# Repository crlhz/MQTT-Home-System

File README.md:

# MQTT Home System

**MQTT Home** is an MQTT based IoT system, developed for the master's thesis. It is a set of devices and programs, which allows to measure physical quantities and control typical home devices. The application of an open-source protocol, such as MQTT, allows a user to add any compatible device to the existing IoT network and gives much more control over transmission and security. The core of the MQTT Home System is **Raspberry Pi**, which runs MQTT Broker, the database and website for measurement presentations and client device’s control. Wireless communication between broker and clients is ensured by a router. A diagram of the example network with three client devices is presented below.

# Client Device - Colibri

The client device, called Colibri, is a microprocessor appliance designed from scratch, providing the measuring and executive functions. For purposes of this thesis, three clients have been assembled and communicated with Raspberry Pi via MQTT protocol. 

## Colibri HW
Colibri is a battery-powered device, which consists of two parts: Power Management Block and CPU Block.

The following inputs/outputs are available for user: 
- J1 - connector for battery charger;
- J2 - UART interface, used for programming device;
- J3 - 1-wire interface, here used as a interface for external temperature sensor;
- J4 - used for enabling deep sleep mode: 1 - 2: sleep mode, 2 - 3: no sleep mode;
- J5 - used for setting boot mode: 1 - 2: standard mode, 2 - 3: programming mode;
- J6 - connector for controlling additional devices (not used in this implementation);
- J7 - connector for 18650 Li-ion battery.

The Power Management Block is responsible for battery charging control and voltage adjustment for the CPU Block. Controller U3 is protecting the battery from being overcharged or over-discharged, by switching U4 and U5 MOSFET transistors, while voltage regulator U6 ensures 3.3V for the CPU Block. The CPU block is responsible for external devices maintenance and broker communication. It’s based on ESP8266 microcontroller, version ESP12 F, which provides a PCB antenna for WiFi transmission. The external resistors are necessary for proper microcontroller operation and they are connected according to the ESP datasheet. A voltage divider, which consists of resistors R8 and R9, is used for measuring battery voltage level. The Colibri software algorithm is presented below.

## Colibri SW
The configuration part allows a user to change topic names and network details, such as SSID, password, broker IP address, and client’s name. After typical variables and interfaces initialization, the program enters an infinite loop, where connection with a broker is established and the measured temperature and voltage is sent to the broker. Finally, the device is going into deep sleep mode for 20 minutes. The described algorithm ensures an acceptable battery life cycle, which can be extended by increasing the sleep time.

## Colibri PCB
Colibri’s PCB has been designed using Kicad software. It is a two layers PCB, which has been assembled by the reflow soldering method. The PCB is enclosed in a KRADEX ABS housing, which provides IP65 protection.

# Broker and subscriber script

The main component of the system is Raspberry Pi, running an MQTT broker called Mosquito, created by the Eclipse Foundation. It’s an open-source implementation of a server for versions 5.0, 3.1.1, and 3.1 of the MQTT protocol. Independently of it, a Python script, called *mqtt_sub_basic.py*, is running on the server. To be more precise, it is a client script, which subscribes to all topics, using the Eclipse Paho MQTT library, also created by Eclipse Foundation. In the beginning, the subscriber script establishes communication with the Mosquito broker and SQL database. Then, by using *client.subscribe("#")*, the script begins subscription of all topics, served by broker. Finally, in an infinite loop, *mqtt_subscribe.py* waits for messages sent by clients in format shown below:

    <topic name>, <measured value>
e.g
    
    blue/temp/out, 22.7
 
Messages received from clients are parsed and then inserted into the SQL database, using methods from the Database class (*db_controller.py* file). This mentioned class is based on the *mysql.connector* library, which allows sending SQL statements from Python scripts to a database. The *mqtt_sub_basic.py* script should be configured as a service, running in the Raspberry Pi’s background, so it starts at every boot-up of the operating system.

# MQTT Home database

The MQTT Home database consists of five tables. It has been developed using a migration mechanism, shared by PHP web framework Laravel. The three tables *users*, *migrations*, *personal_access_tokens* are default Laravel composition, which allows user and migration management. Furthermore, the table users has been implemented, with future development needs in mind, such as adding new topics via the website by logged-in users. The table *topics* stores available topic names, which can be used by client devices. For this system, the following topic format has been adopted.

Additionally, for convenient data presentation, the column unit has been defined in the topics table. The table measurements stores data received from clients via the mentioned Python script.

# MQTT Home website

The MQTT Home website is another important component of the entire system. Its main goal is to present collected data in a user-friendly and convenient way. Furthermore, in case of future development, it may provide some setup functionality, such as topics and users configuration. The website has been created using Laravel, an open-source PHP framework, designed according to the model-view-controller (MVC) architectural pattern. This improves its scalability and resolves many development issues related to cybersecurity, database connections, etc. The homepage, follows a grid layout, which is dynamically generated depending on the topic’s number. Each box stands for a single topic and contains the latest measurement. In a case of communication loss (i.e., 20 minutes or more without a new message), the label N/A is displayed. Apart from values, the boxes include topic names and units.

By clicking on a specific box, the user is able to open the chart view. The charts implementation is based on the Highcharts library. For the sake of clarity of the chart, the displayed data are from the last three days only.

The website’s project consists of three controllers: *Controller.php*, which is created by default as a Laravel Base Controller, together with *MainController.php* and *ChartController.php*, that form the core of the whole application. Both are responsible for retrieving data from the database, processing them into appropriate form and passing to the frontend section. This section is developed by using the Blade templates engine. In the *app.blade.php* file, the overall template of the website was designed, while in *main.blade.php* and *chart.blade.php* the specific content of both views is described. As mentioned before, the homepage consists of boxes representing every available topic. Clicking on any of them redirects to *home.test/chart/n*, where *n* stands for the topic identifier. At this address, a chart related to the chosen topic is displayed. The website project scheme is presented below.

# Server configuration
The last but not least element of the MQTT Home System is the server system. It provides the following functionality: 
- running MQTT broker service;
- receiving data from clients;
- storing received data in the SQL database;
- running WWW service;
- presenting stored data on the website. 

Considering the price and energy consumption, the Raspberry Pi 4B SBC was chosen as the server hardware. This particular SBC is equipped with 4GB of RAM and runs a 1.5 GHz, 64-bit quad core ARM Cortex-A72 processor. Its capabilities exceed the current requirements of this application, but it may be an optimal choice for future development. As mentioned before, the MQTT broker service is run by Eclipse Mosquitto, installed according to the instructions described in the documentation. Afterwards, the default configuration has been applied. In the next step, Python v3.9.2 with *paho.mqtt.client* and *mysql.connector* libraries have been installed. MariaDB v10.5.12 was used as a relational database management system in connection with the phpMyAdmin service. The WWW server functionality has been built upon the LAMP software stack: Linux + Apache + MariaDB + PHP. Therefore, the last step was to install Apache v2.4.52 and PHP v8.1.3. The MQTT Home System website is running as an Apache virtual host on the default TCP port 80.

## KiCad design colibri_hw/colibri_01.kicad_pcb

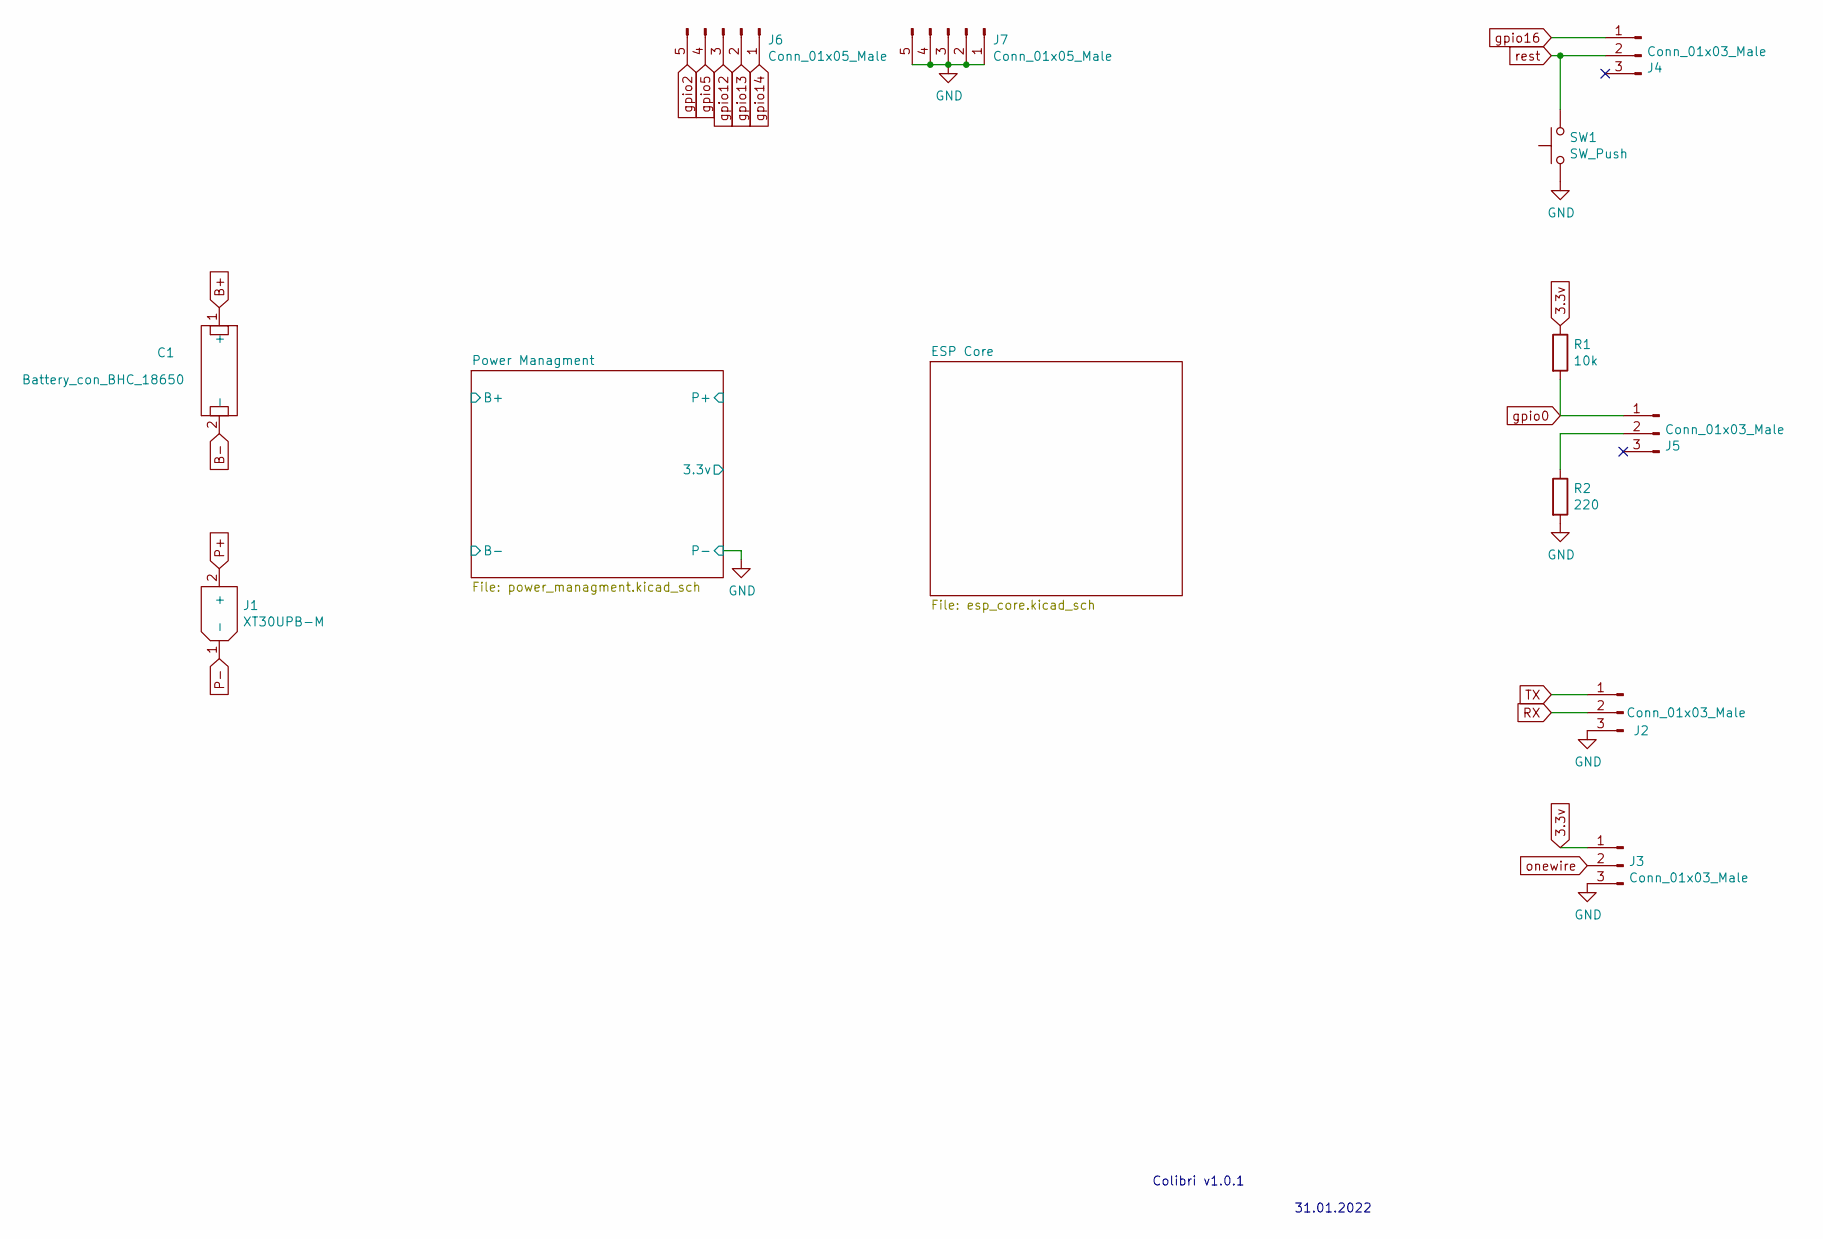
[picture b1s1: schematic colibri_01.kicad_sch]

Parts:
C1: Battery_con_BHC_18650
J1: XT30UPB-M; AMASS_XT30UPB-M_1x02_P5.0mm_Vertical
J2, J3, J4, J5: Conn_01x03_Male; PinHeader_1x03_P2.54mm_Vertical
J6, J7: Conn_01x05_Male; PinHeader_1x05_P2.54mm_Vertical
R1: 10k; R_0805_2012Metric
R2: 220; R_0805_2012Metric
SW1: SW_Push; TP-1163s

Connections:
3.3v: J3.1, R1.1; also elsewhere on the board
B+: C1.1 (+), J1.2 (+); also elsewhere on the board
B-: C1.2 (-); also elsewhere on the board
unnamed: J5.2, R2.1
RX: J2.2; also elsewhere on the board
TX: J2.1; also elsewhere on the board
gpio0: J5.1, R1.2; also elsewhere on the board
gpio2: J6.5; also elsewhere on the board
gpio5: J6.4; also elsewhere on the board
gpio12: J6.3; also elsewhere on the board
gpio13: J6.2; also elsewhere on the board
gpio14: J6.1; also elsewhere on the board
gpio16: J4.1; also elsewhere on the board
onewire: J3.2; also elsewhere on the board
rest: J4.2, SW1.2; also elsewhere on the board

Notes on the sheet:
Colibri v1.0.1
31.01.2022

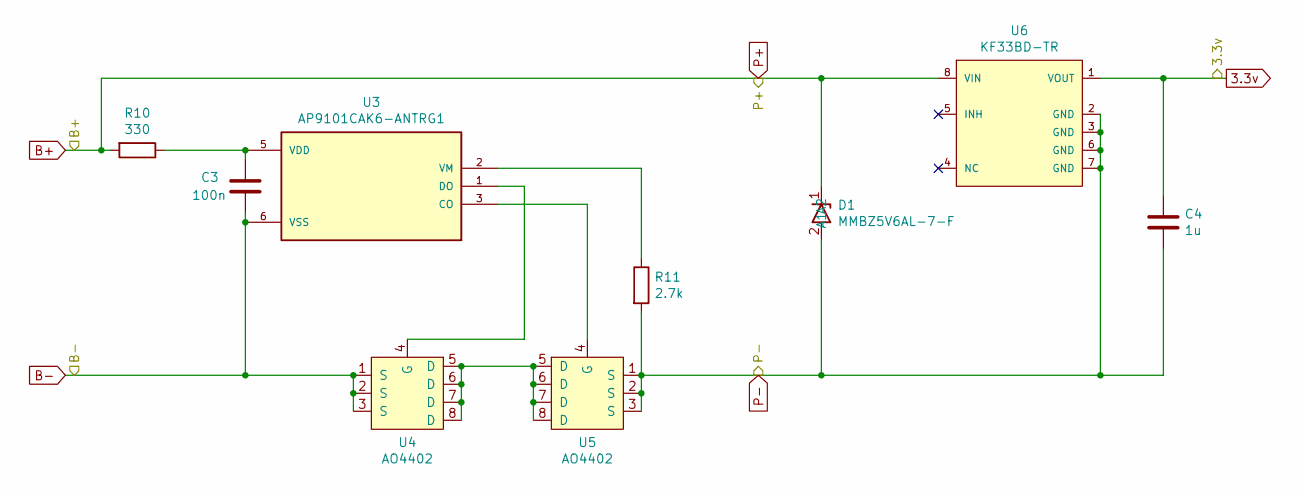
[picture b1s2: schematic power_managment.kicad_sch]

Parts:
C3: 100n; C_1206_3216Metric
C4: 1u; C_1206_3216Metric_Pad1.33x1.80mm_HandSolder
D1: MMBZ5V6AL-7-F; SOT-23
R10: 330; R_0805_2012Metric
R11: 2.7k; R_0805_2012Metric
U3: AP9101CAK6-ANTRG1; SOT-23-6
U4, U5: AO4402; SOIC127P490X600X175-8N
U6: KF33BD-TR; STMicroelectronics-KF33BD-TR-Level_A

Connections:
3.3v: C4.1, U6.1 (VOUT); also elsewhere on the board
B+: D1.1 (A1), R10.2, U6.8 (VIN); also elsewhere on the board
B-: C3.1, U3.6 (VSS), U4.1 (S), U4.2 (S), U4.3 (S); also elsewhere on the board
unnamed: C3.2, R10.1, U3.5 (VDD)
unnamed: R11.1, U3.2 (VM)
unnamed: U3.1 (DO), U4.4 (G)
unnamed: U3.3 (CO), U5.4 (G)
unnamed: U4.5 (D), U4.6 (D), U4.7 (D), U4.8 (D), U5.5 (D), U5.6 (D), U5.7 (D), U5.8 (D)

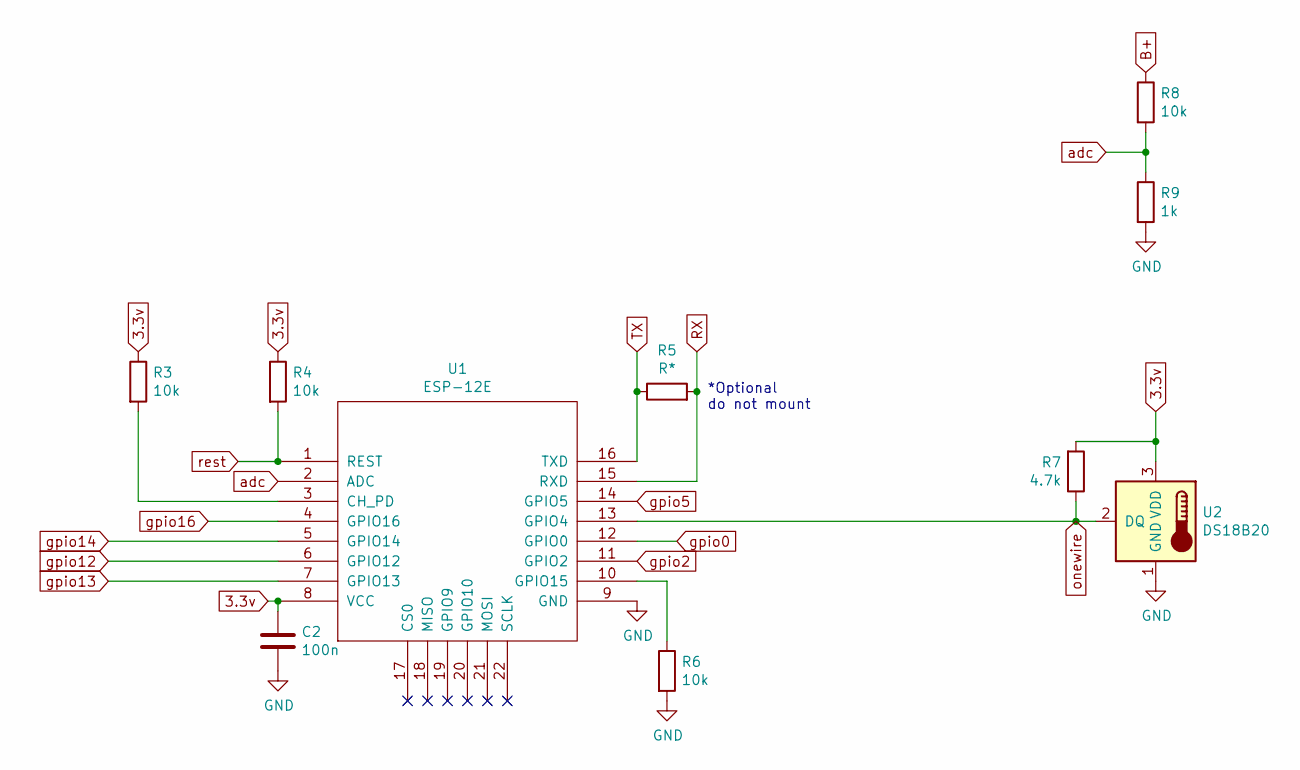
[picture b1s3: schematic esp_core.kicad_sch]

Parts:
C2: 100n; C_1206_3216Metric
R3, R4, R6, R8: 10k; R_0805_2012Metric
R5: R*; R_0805_2012Metric
R7: 4.7k; R_0805_2012Metric
R9: 1k; R_0805_2012Metric
U1: ESP-12E; ESP-12E_SMD
U2: DS18B20; TO-92

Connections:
3.3v: C2.1, R3.1, R4.1, R7.2, U1.8 (VCC), U2.3 (VDD); also elsewhere on the board
B+: R8.1; also elsewhere on the board
unnamed: R3.2, U1.3 (CH_PD)
unnamed: R6.1, U1.10 (GPIO15)
RX: R5.2, U1.15 (RXD); also elsewhere on the board
TX: R5.1, U1.16 (TXD); also elsewhere on the board
adc: R8.2, R9.1, U1.2 (ADC)
gpio0: U1.12 (GPIO0); also elsewhere on the board
gpio2: U1.11 (GPIO2); also elsewhere on the board
gpio5: U1.14 (GPIO5); also elsewhere on the board
gpio12: U1.6 (GPIO12); also elsewhere on the board
gpio13: U1.7 (GPIO13); also elsewhere on the board
gpio14: U1.5 (GPIO14); also elsewhere on the board
gpio16: U1.4 (GPIO16); also elsewhere on the board
onewire: R7.1, U1.13 (GPIO4), U2.2 (DQ); also elsewhere on the board
rest: R4.2, U1.1 (REST); also elsewhere on the board

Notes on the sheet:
*Optional do not mount

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
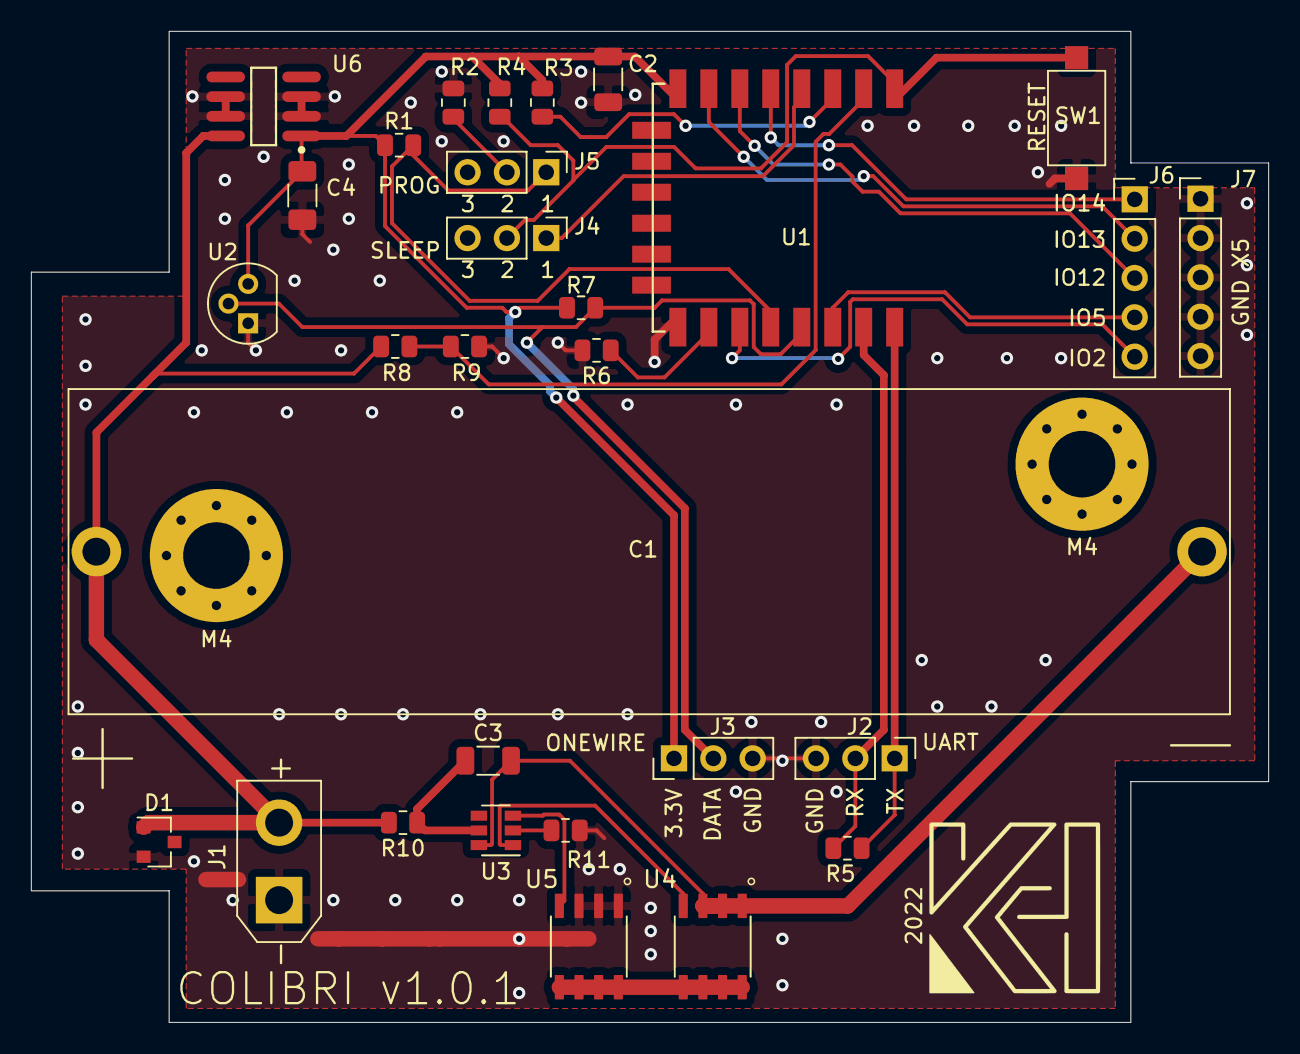
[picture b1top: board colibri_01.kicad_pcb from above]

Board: 2 copper layers, 79.9 x 64.0 mm, 32 parts (0 on the bottom side), 24 nets.

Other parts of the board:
M4, M4#2: MountingHole_4.3mm_M4_Pad_Via

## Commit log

2022-10-28 [v1.0.0]
2022-10-28 [v1.0.1]: Fix UART communication issues due to R5 value
2022-10-31 Create LICENSE
